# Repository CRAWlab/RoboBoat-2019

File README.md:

This repository contains code used by the [University of Louisiana at Lafayette](http://louisiana.edu) team in the 2019 [RoboBoat](https://www.robonation.org/competition/roboboat) Contest.

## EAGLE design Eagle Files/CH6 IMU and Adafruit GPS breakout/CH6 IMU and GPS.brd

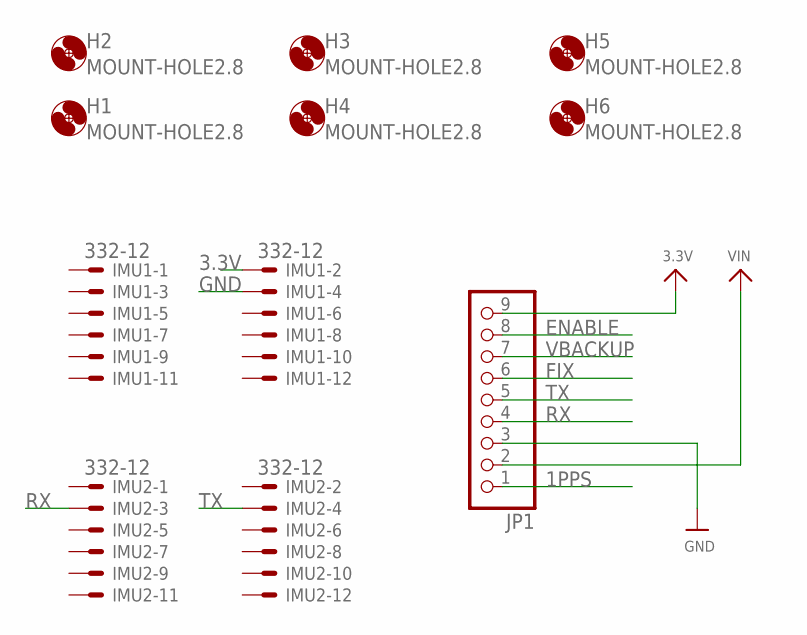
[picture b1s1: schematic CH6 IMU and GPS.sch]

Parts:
H1, H2, H3, H4, H5, H6: MOUNT-HOLE2.8; 2,8
IMU1, IMU2: 332-12
JP1: HEADER-1X970MIL; 1X09_ROUND_70

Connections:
1PPS: JP1.1
3.3V: IMU1.2, JP1.9
ENABLE: JP1.8
FIX: JP1.6
GND: IMU1.4, JP1.3
RX: IMU2.3, JP1.4
TX: IMU2.4, JP1.5
VBACKUP: JP1.7
VIN: JP1.2

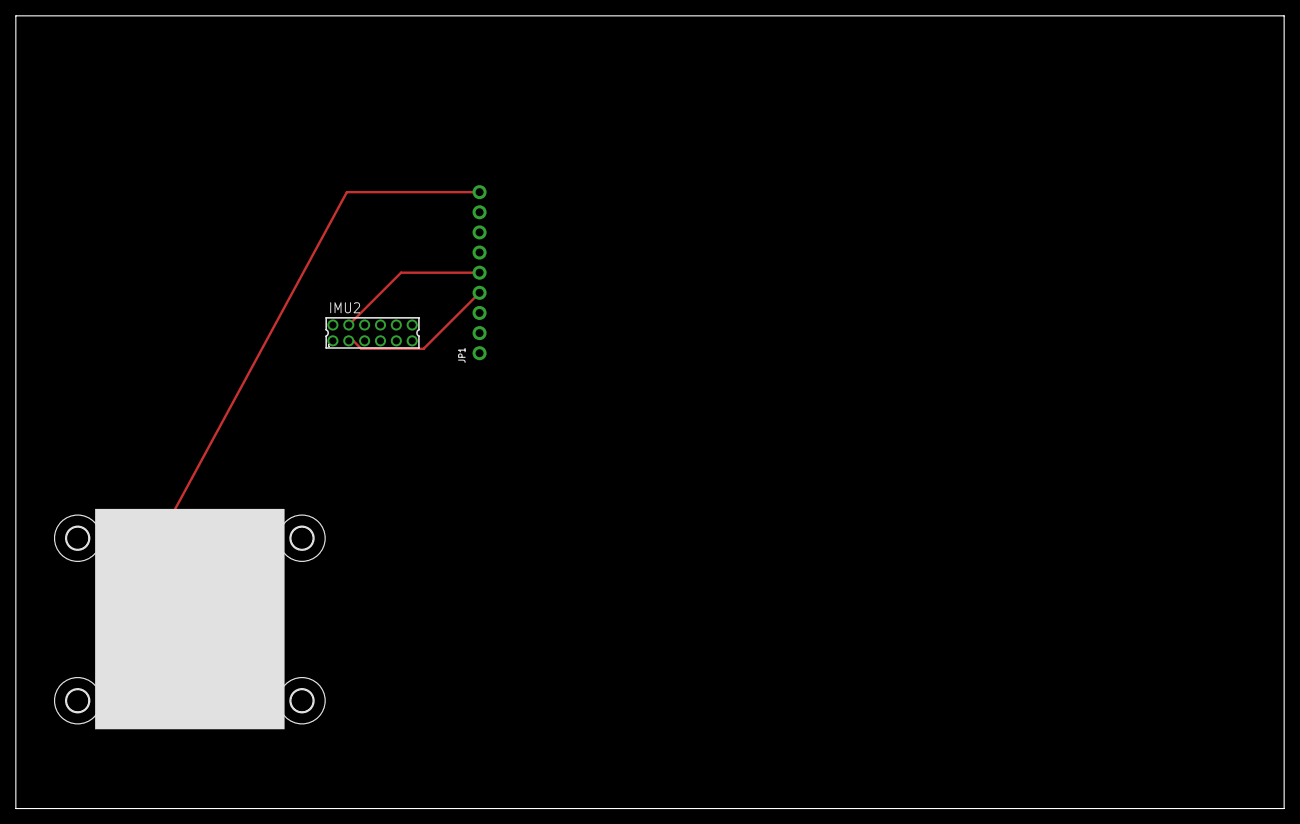
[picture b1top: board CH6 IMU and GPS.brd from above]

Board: 2 copper layers, 160.0 x 100.0 mm, 9 parts (0 on the bottom side), 4 nets.

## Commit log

2019-04-20 Added basic T200 thruster control - untested
2019-04-20 Initial commit of CH6 and GPS breakout board PCB
2019-04-20 Working BlueRobotics T200 single thruster
    TODO:
    - 0.4 throttle is being interpreted as zero. Likely due to:
    + PWM timing in Adafruit library or
    + range of pulse width set
    - Account for thruster deadzone around zero throttle
    - Check limits on forward and reverse speeds
2019-04-22 Reorganized to differentiate between pure Python and ROS code
2019-04-22 IN-PROGRESS: Work toward updating UM6 IMU to Python 3
2019-04-24 WORK IN PROGRESS - Continued conversion of UM6 script to Python3
2019-04-28 Added basic thrust mapping for X-config
2019-05-02 Initial mapping of cmd_vel messages to X-config thrusters
    TODO:
    * Test
    * Fix throttle offset issue
    * Check thruster positioning
    * Clean up thrust and velocities to match the actual limits
    * Vectorize thruster definitions
2019-05-02 Typo corection
2019-05-02 Thruster mappting logic tested in Gazebo - working
2019-05-02 Typo correction
2019-05-04 Implemented fix for thruster offset - Tested and working
    TODO:
    - Check that throttle fix allows full range of thruster speeds
2019-05-14 Deleted backup script for UM7 IMU
2019-05-15 Update RoboBoat_cmd_vel_to_thrusters.py
    Set offset to 0, fixed a typo, changed max velocities for better control, changed stbd thruster to correct inputs
2019-05-15 ROS workspace
    Added the ROS workspace with the joystick code we used for testing, added deadman button RT (untested)
2019-05-15 Revert "ROS workspace"
    This reverts commit be96512250bcbd3bb1003a920f2c38a946b5c669.
2019-05-15 Added ROS controller package
    Added the code we used to read the controller for testing, added deadman button RT (untested)
2019-05-16 Initial commit of LoRA-based E-stop system
    TODO:
    * Add Relay control to the receiver
    * Add serial comm. for status reporting to receiver
2019-05-17 Added serial comm of status with LoRa board, serial test script
    TODO:
    * Clean up data sent for application
    * double-check timing
    * more efficiently assign colors
2019-05-17 Added relay control to E-stop LoRa receiver - untested
2019-06-04 Simple check of LED-button in E-stop remote
2019-06-05 Added E-stop button and LED to E-stop heartbeat sender
2019-06-05 Added status check of hardwired E-stops
2019-06-05 Updated to loop timing on E-stop system
2019-06-11 Added tf.launch
2019-06-11 Added UM7 with GPS
2019-06-13 Work on packaging of UM7 node with GPS
    * Import still only works as direct python call
2019-06-13 Coding Skeleton (First iteration)
    Very basic thought through all tasks required by the competition.
2019-06-14 Updated tf and added urg_node
    Made corrections to transform and added the urg_node with the lidar's IP in the launch file
2019-06-14 Initial outline of status report to TD, finished checksum calculation
2019-06-14 Near final, but untested status reporter.
    TODO:
    * Add parsing of the boat's /status message
    * Test socket performance
2019-06-15 Reversed brightness on E-stop light
2019-06-17 Added mode callback to TD communication node
2019-06-17 Added dock and flag to TD comm. node
2019-06-17 Updated formatting to Coding Skeleton
2019-06-17 Added text files for on-site testing
2019-06-17 Added tmux.conf to allow strolling
2019-06-17 Added .bashrc commands for easy use
2019-06-17 renamed tmux setting explanation file
2019-06-18 Typo fix
2019-06-18 Test-ready version of script to publish to TD server
    TODO:
    * Test by just running with Python from the command line
    * Convert to ROS node
2019-06-18 Typo fix in TD message sender
2019-06-18 Initial commit of RaspPi <-> LoRa system comm node
2019-06-18 Added launch files
    base.launch confirmed working
2019-06-18 Adjusted for CCW thrusters (untested)
2019-06-18 Clarity edits to TD server communication node
2019-06-18 Updates to communication script with E-stop system
2019-06-18 Updated LORA heartbeat receiver to send current status
2019-06-18 typo correction in Raspberry pi Launch file
2019-06-18 Added rosbridge to Jetson launch file
2019-06-18 E-stop comms and TD status server to ROS nodes
2019-06-18 Updates to suggested rosbag command and Tuesday's tests outline
2019-06-19 Updated LoRa heartbeat Ardunio for concise serial comm
2019-06-19 Updates to estop_comms script/node for day 1 testing
2019-06-19 Update to list scripts to run on Raspberry Pi if launch file is absent
2019-06-19 Fixed ==
2019-06-19 added thrust map to raspberry pi list
2019-06-19 Fixed typo in rosbag command
2019-06-19 Added explanation of saving rosbag files to the micro-sd card on the Jetson
2019-06-20 Initial commit of navigation package - Untested
    Largely a copy of that on the Husky. See the tutorials there for use.
2019-06-20 Initial commit of vizualization node - Still needs description node (URDF) to work
2019-06-20 Initial commit of control node - untested
2019-06-20 Update Coding Skeleton
    added comments to skeleton
2019-06-20 Update rosbag filesize and added Pi temp check to testing folder
2019-06-21 Update Coding Skeleton
    formatted all sections and added revisions to:
    *autonav
    *circumnav
    *slolam
2019-06-21 Added zed/zed_node/odom to standard rosbag commands
2019-06-21 Update to default rosbag commands
2019-06-22 Update to rosbag defaults
2019-06-22 Added launchfile to pull all images from a bagfile
2019-06-22 Updated localization to include GPS
2019-06-22 Updates to costmap and planner configurations
2019-06-22 Moved Raspberry Pi temperature script info to README.md
2019-06-22 GPS odometry should be numbered
2019-06-22 updated localization to more closely match Husky
2019-06-22 updates to configuration based on Clearpath Heron
2019-06-22 Updates based on Heron
2019-06-22 Update to planner update frequency
    Based on: http://answers.ros.org/question/247116/how-can-i-reduce-drift-in-my-robots-trajectory/
2019-06-22 Updated to localization settings to current best
2019-06-22 Initial commit of Raspberry Pi tmux bash script
2019-06-22 Qualifying Round navigation and planning configurations
2019-06-22 Update to rpi tmux launcher to automatically source ROS install
2019-06-22 Added bash script to monitor Raspberry Pi temperature from the terminal
2019-06-22 cleanup Raspberry Pi temp script
2019-06-22 Create speed.py
    Script used to attempt speed challange
2019-06-22 Added status/LED publication to speed.py move_base script
2019-06-23 Create GPS Task Way Points (Course A)
    GPS coordinates for all task starts and boundary markers
2019-06-23 Update and rename GPS Task Way Points (Course A) to GPS_Task_Way_Points
    added courses B and C
2019-06-23 Added basic GPS-aided navigation - untested
2019-06-23 Name change to better reflect usage
2019-06-23 navigation_supervisor from Sunday - untested due to 🔥
2019-07-25 Renaming folders to match ROS conventions
2019-07-26 Continued reorganization and renaming to match ROS conventions
2020-03-18 Updated RobotBot_thrust control allocation script to match competition version
